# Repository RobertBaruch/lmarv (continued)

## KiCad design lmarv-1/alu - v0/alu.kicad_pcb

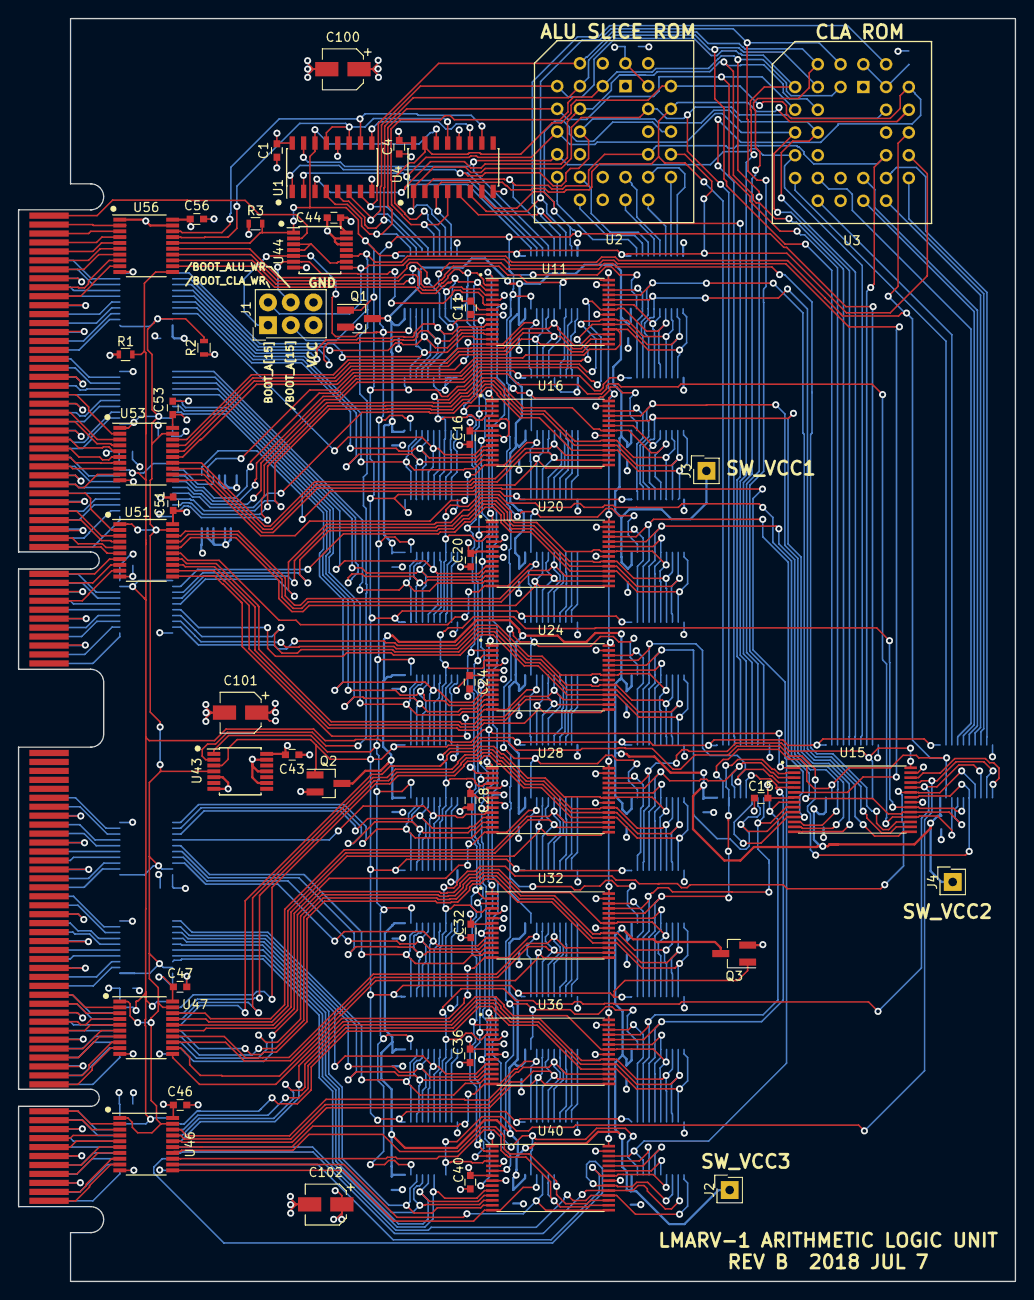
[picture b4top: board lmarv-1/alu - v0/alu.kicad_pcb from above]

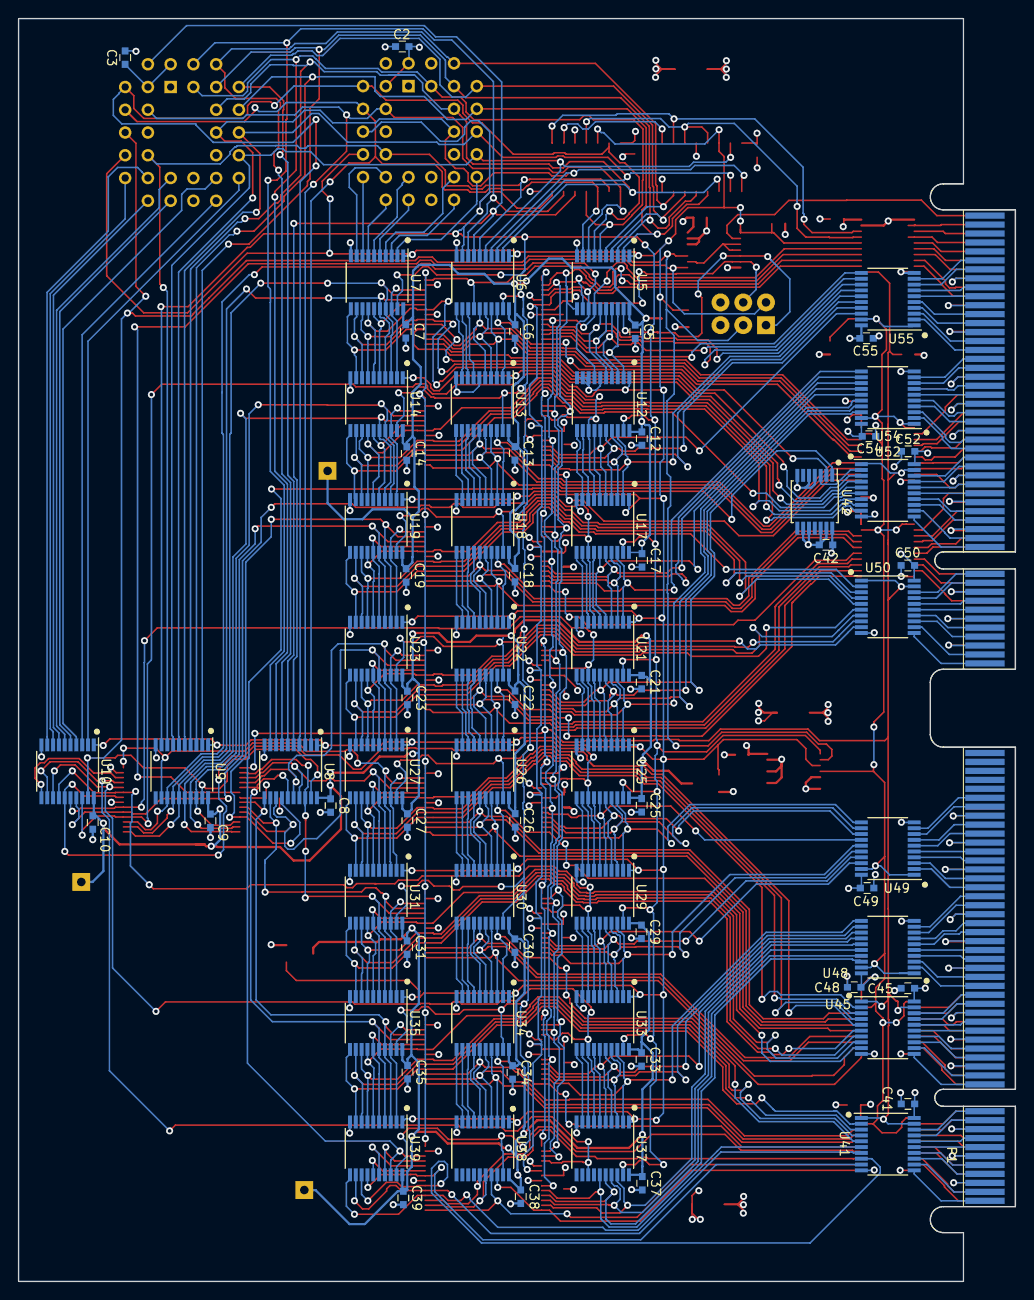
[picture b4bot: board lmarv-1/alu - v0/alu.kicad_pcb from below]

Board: 4 copper layers, 111.3 x 141.0 mm, 126 parts (75 on the bottom side), 339 nets.

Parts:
C1, C2, C3, C4, C5, C6, C7, C8, C9, C10, C11, C12, C13, C14, C15, C16, C17, C18, C19, C20, C21, C22, C23, C24, C25, C26, C27, C28, C29, C30, C31, C32, C33, C34, C35, C36, C37, C38, C39, C40, C41, C42, C43, C44, C45, C46, C47, C48, C49, C50, C51, C52, C53, C54, C55, C56: 0u1; C_0603
C100, C101, C102: 1u; CP_Elec_4x4.5
J1: Conn_02x03_Odd_Even; SDL-106-X-XX_2x03
J2, J3, J4: Conn_01x01; SL-101-X-XX_1x01
P1: dual-pcie-cardedge; PCI-EXPRESS
Q1, Q2, Q3: DMP3056L; SOT-23_Handsoldering
R1, R2, R3: 10k; R_0603
U1, U4: 74HC590; SOIC-16_3.9x9.9mm_Pitch1.27mm
U2: AT28BV64B-20JU; PLCC32
U3: AT28BV256B-20JU; PLCC32
U5, U6, U7, U8, U9, U10, U12, U13, U14, U17, U18, U19, U21, U22, U23, U25, U26, U27, U29, U30, U31, U33, U34, U35, U37, U38, U39, U41, U45, U46, U47, U48, U49, U50, U51, U52, U53, U54, U55, U56: 74LVC541; TSSOP-20_4.4x6.5mm_Pitch0.65mm
U11, U15, U16, U20, U24, U28, U32, U36, U40: IS61LV256AL; TSOP-I-28_18.4x8mm_Pitch0.55mm
U42, U44: 74LVC32; TSSOP-14_4.4x5mm_Pitch0.65mm
U43: 74LVC04; TSSOP-14_4.4x5mm_Pitch0.65mm

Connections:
/BOOT_ALU_EN: R2.2, U43.4, U46.1, U46.19, U47.1, U47.19, U48.1, U48.19, U49.1, U49.19, U51.1, U51.19, U53.1, U53.19, U54.1, U54.19, U55.1, U55.19
/BOOT_A[0]: U1.15, U2.11, U3.11, U6.5, U9.7
/BOOT_A[1]: U1.1, U2.10, U3.10, U6.4, U9.6
/BOOT_A[2]: U1.2, U2.9, U3.9, U6.3, U9.5
/BOOT_A[3]: U1.3, U2.8, U3.8, U6.2, U9.4
/BOOT_A[4]: U1.4, U2.7, U3.7, U5.2, U9.3
/BOOT_A[5]: U1.5, U2.6, U3.6, U5.3, U9.2
/BOOT_A[6]: U1.6, U2.5, U3.5, U5.4, U8.6
/BOOT_A[7]: U1.7, U2.4, U3.4, U5.5, U8.7
/BOOT_A[8]: U2.29, U3.29, U4.15, U5.7, U8.4
/BOOT_A[9]: U2.28, U3.28, U4.1, U5.8, U8.3
/BOOT_A[10]: U2.24, U3.24, U4.2, U6.6, U9.8
/BOOT_A[11]: U2.27, U3.27, U4.3, U5.9, U8.2
/BOOT_A[12]: U2.3, U3.3, U4.4, U5.6, U8.8
/BOOT_A[13]: U3.30, U4.5, U6.7, U8.5
/BOOT_A[14]: U3.2, U4.6, U6.8, U8.9
/BOOT_A[15]: J1.1, U2.25, U4.7, U5.19, U6.9, U6.19, U7.19, U9.9, U12.19, U13.19, U14.19, U17.19, U18.19, U19.19, U21.19, U22.19, U23.19, U25.19, U26.19, U27.19, U29.19, U30.19, U31.19, U33.19, U34.19, U35.19, U37.19, U38.19, U39.19, U43.1, U44.5
/BOOT_CLK: U1.11, U1.13, U4.13, U56.17
/BOOT_CLK': P1.194, U56.3
/CLA_D0: U3.13, U10.2
/CLA_D1: U3.14, U10.3
/CLA_D2: U3.15, U10.4
/CLA_D3: U3.18, U10.5
/CLA_D4: U3.19, U10.6
/CLA_D5: U3.20, U10.7
/CLA_D6: U3.21, U10.8
/CLA_D7: U3.22, U10.9
/SLICE_D0: U2.13, U7.2
/SLICE_D1: U2.14, U7.3
/SLICE_D2: U2.15, U7.4
/SLICE_D3: U2.18, U7.5
/SLICE_D4: U2.19, U7.6
/SLICE_D5: U2.20, U7.7
/SLICE_D6: U2.21, U7.8
/SLICE_D7: U2.22, U7.9
/SW_VCC1: C5.1, C6.1, C7.1, C12.1, C13.1, C14.1, C17.1, C18.1, C19.1, J3.1, Q1.3, U5.20, U6.20, U7.20, U12.20, U13.20, U14.20, U17.20, U18.20, U19.20
/SW_VCC2: C8.1, C9.1, C10.1, C21.1, C22.1, C23.1, C25.1, C26.1, C27.1, J4.1, Q2.3, U8.20, U9.20, U10.20, U21.20, U22.20, U23.20, U25.20, U26.20, U27.20
/SW_VCC3: C29.1, C30.1, C31.1, C33.1, C34.1, C35.1, C37.1, C38.1, C39.1, J2.1, Q3.3, U29.20, U30.20, U31.20, U33.20, U34.20, U35.20, U37.20, U38.20, U39.20
/alu_f[0]: U5.12, U11.24, U16.24, U20.24, U24.24, U28.24, U32.24, U36.24, U40.24, U56.12
/alu_f[1]: U6.14, U11.21, U16.21, U20.21, U24.21, U28.21, U32.21, U36.21, U40.21, U56.13
/alu_f[2]: U5.11, U11.23, U16.23, U20.23, U24.23, U28.23, U32.23, U36.23, U40.23, U56.14
/alu_f[3]: U5.14, U11.2, U16.2, U20.2, U24.2, U28.2, U32.2, U36.2, U40.2, U56.15
/cin[0]: U5.13, U9.13, U11.25, U12.7, U15.10
/cin[1]: U10.18, U12.13, U15.11, U16.25, U17.7
/cin[2]: U10.17, U15.12, U17.13, U20.25, U21.7
/cin[3]: U10.16, U15.13, U21.13, U24.25, U25.7
/cin[4]: U10.15, U15.15, U25.13, U28.25, U29.7
/cin[5]: U10.14, U15.16, U29.13, U32.25, U33.7
/cin[6]: U10.13, U15.17, U33.13, U36.25, U37.7
/cin[7]: U10.12, U15.18, U37.13, U40.25
/cout[0]: U7.15, U11.16, U14.5
/cout[1]: U14.15, U16.16, U19.5
/cout[2]: U19.15, U20.16, U23.5
/cout[3]: U23.15, U24.16, U27.5
/cout[4]: U27.15, U28.16, U31.5
/cout[5]: U31.15, U32.16, U35.5
/cout[6]: U35.15, U36.16, U39.5
/cout[7]: U39.15, U40.16
/f[0]: P1.188, U56.8
/f[1]: P1.190, U56.7
/f[2]: P1.191, U56.6
/f[3]: P1.192, U56.5
/g[0]: U7.17, U9.15, U11.18, U14.3, U15.8
/g[1]: U9.17, U14.17, U15.6, U16.18, U19.3
/g[2]: U8.14, U15.4, U19.17, U20.18, U23.3
/g[3]: U8.16, U15.25, U23.17, U24.18, U27.3
/g[4]: U9.12, U15.21, U27.17, U28.18, U31.3
/g[5]: U8.12, U15.2, U31.17, U32.18, U35.3
/g[6]: U8.11, U15.1, U35.17, U36.18, U39.3
/g[7]: U39.17, U40.18
/lt[0]: U7.18, U11.19, U14.2
/lt[1]: U14.18, U16.19, U19.2
/lt[2]: U19.18, U20.19, U23.2
/lt[3]: U23.18, U24.19, U27.2
/lt[4]: U27.18, U28.19, U31.2
/lt[5]: U31.18, U32.19, U35.2
/lt[6]: U35.18, U36.19, U39.2
/lt[7]: U39.18, U40.19, U42.1
/p[0]: U7.16, U9.14, U11.17, U14.4, U15.9
/p[1]: U9.16, U14.16, U15.7, U16.17, U19.4
/p[2]: U9.18, U15.5, U19.16, U20.17, U23.4
/p[3]: U8.13, U15.3, U23.16, U24.17, U27.4
/p[4]: U8.17, U15.24, U27.16, U28.17, U31.4
/p[5]: U8.18, U15.23, U31.16, U32.17, U35.4
/p[6]: U8.15, U15.26, U35.16, U36.17, U39.4
/p[7]: U39.16, U40.17
/rd[0]: P1.71, U52.18
/rd[1]: P1.70, U52.17
/rd[2]: P1.68, U52.16
/rd[3]: P1.67, U52.15
/rd[4]: P1.65, U52.14
/rd[5]: P1.64, U52.13
/rd[6]: P1.62, U52.12
/rd[7]: P1.61, U52.11
/rd[8]: P1.60, U50.18
/rd[9]: P1.59, U50.17
/rd[10]: P1.57, U50.16
/rd[11]: P1.56, U50.15
/rd[12]: P1.54, U50.14
/rd[13]: P1.53, U50.13
/rd[14]: P1.51, U50.12
/rd[15]: P1.50, U50.11
/rd[16]: P1.22, U45.18
/rd[17]: P1.21, U45.17
/rd[18]: P1.19, U45.16
/rd[19]: P1.18, U45.15
/rd[20]: P1.16, U45.14
/rd[21]: P1.15, U45.13
/rd[22]: P1.13, U45.12
/rd[23]: P1.12, U45.11
/rd[24]: P1.11, U41.18
/rd[25]: P1.10, U41.17
/rd[26]: P1.8, U41.16
/rd[27]: P1.7, U41.15
/rd[28]: P1.5, U41.14
/rd[29]: P1.4, U41.13
/rd[30]: P1.2, U41.12
/rd[31]: P1.1, U41.11
/rdb[0]: U42.3, U52.2
/rdb[0]': U7.11, U11.11, U14.9, U42.2
/rdb[1]: U7.12, U11.12, U14.8, U52.3
/rdb[2]: U7.13, U11.13, U14.7, U52.4
/rdb[3]: U7.14, U11.15, U14.6, U52.5
/rdb[4]: U14.11, U16.11, U19.9, U52.6
/rdb[5]: U14.12, U16.12, U19.8, U52.7
/rdb[6]: U14.13, U16.13, U19.7, U52.8
/rdb[7]: U14.14, U16.15, U19.6, U52.9
/rdb[8]: U19.11, U20.11, U23.9, U50.2
/rdb[9]: U19.12, U20.12, U23.8, U50.3
/rdb[10]: U19.13, U20.13, U23.7, U50.4
/rdb[11]: U19.14, U20.15, U23.6, U50.5
/rdb[12]: U23.11, U24.11, U27.9, U50.6
/rdb[13]: U23.12, U24.12, U27.8, U50.7
/rdb[14]: U23.13, U24.13, U27.7, U50.8
/rdb[15]: U23.14, U24.15, U27.6, U50.9
/rdb[16]: U27.11, U28.11, U31.9, U45.2
/rdb[17]: U27.12, U28.12, U31.8, U45.3
/rdb[18]: U27.13, U28.13, U31.7, U45.4
/rdb[19]: U27.14, U28.15, U31.6, U45.5
/rdb[20]: U31.11, U32.11, U35.9, U45.6
/rdb[21]: U31.12, U32.12, U35.8, U45.7
/rdb[22]: U31.13, U32.13, U35.7, U45.8
/rdb[23]: U31.14, U32.15, U35.6, U45.9
/rdb[24]: U35.11, U36.11, U39.9, U41.2
/rdb[25]: U35.12, U36.12, U39.8, U41.3
/rdb[26]: U35.13, U36.13, U39.7, U41.4
/rdb[27]: U35.14, U36.15, U39.6, U41.5
/rdb[28]: U39.11, U40.11, U41.6
/rdb[29]: U39.12, U40.12, U41.7
/rdb[30]: U39.13, U40.13, U41.8
/rdb[31]: U39.14, U40.15, U41.9
/rs1[0]: P1.176, U53.2
/rs1[1]: P1.174, U53.3
/rs1[2]: P1.173, U53.4
/rs1[3]: P1.171, U53.5
/rs1[4]: P1.170, U53.6
/rs1[5]: P1.169, U53.7
/rs1[6]: P1.168, U53.8
/rs1[7]: P1.166, U53.9
/rs1[8]: P1.165, U51.2
/rs1[9]: P1.163, U51.3
/rs1[10]: P1.162, U51.4
/rs1[11]: P1.160, U51.5
/rs1[12]: P1.159, U51.6
/rs1[13]: P1.158, U51.7
/rs1[14]: P1.157, U51.8
/rs1[15]: P1.155, U51.9
/rs1[16]: P1.120, U47.2
/rs1[17]: P1.119, U47.3
/rs1[18]: P1.117, U47.4
/rs1[19]: P1.116, U47.5
/rs1[20]: P1.114, U47.6
/rs1[21]: P1.113, U47.7
/rs1[22]: P1.111, U47.8
/rs1[23]: P1.110, U47.9
/rs1[24]: P1.109, U46.2
/rs1[25]: P1.108, U46.3
/rs1[26]: P1.106, U46.4
/rs1[27]: P1.105, U46.5
/rs1[28]: P1.103, U46.6
/rs1[29]: P1.102, U46.7
/rs1[30]: P1.100, U46.8
/rs1[31]: P1.99, U46.9
/rs1b[0]: U6.15, U11.10, U13.5, U53.18
/rs1b[1]: U6.16, U11.9, U13.4, U53.17
/rs1b[2]: U6.17, U11.8, U13.3, U53.16
/rs1b[3]: U6.18, U11.7, U13.2, U53.15
/rs1b[4]: U13.15, U16.10, U18.5, U53.14
/rs1b[5]: U13.16, U16.9, U18.4, U53.13
/rs1b[6]: U13.17, U16.8, U18.3, U53.12
/rs1b[7]: U13.18, U16.7, U18.2, U53.11
/rs1b[8]: U18.15, U20.10, U22.5, U51.18
/rs1b[9]: U18.16, U20.9, U22.4, U51.17
/rs1b[10]: U18.17, U20.8, U22.3, U51.16
/rs1b[11]: U18.18, U20.7, U22.2, U51.15
/rs1b[12]: U22.15, U24.10, U26.5, U51.14
/rs1b[13]: U22.16, U24.9, U26.4, U51.13
/rs1b[14]: U22.17, U24.8, U26.3, U51.12
/rs1b[15]: U22.18, U24.7, U26.2, U51.11
/rs1b[16]: U26.15, U28.10, U30.5, U47.18
/rs1b[17]: U26.16, U28.9, U30.4, U47.17
/rs1b[18]: U26.17, U28.8, U30.3, U47.16
/rs1b[19]: U26.18, U28.7, U30.2, U47.15
/rs1b[20]: U30.15, U32.10, U34.5, U47.14
/rs1b[21]: U30.16, U32.9, U34.4, U47.13
/rs1b[22]: U30.17, U32.8, U34.3, U47.12
/rs1b[23]: U30.18, U32.7, U34.2, U47.11
/rs1b[24]: U34.15, U36.10, U38.5, U46.18
/rs1b[25]: U34.16, U36.9, U38.4, U46.17
/rs1b[26]: U34.17, U36.8, U38.3, U46.16
/rs1b[27]: U34.18, U36.7, U38.2, U46.15
/rs1b[28]: U38.15, U40.10, U46.14
/rs1b[29]: U38.16, U40.9, U46.13
/rs1b[30]: U38.17, U40.8, U46.12
/rs1b[31]: U38.18, U40.7, U46.11
/rs2[0]: P1.93, U55.9
/rs2[1]: P1.92, U55.8
/rs2[2]: P1.90, U55.7
/rs2[3]: P1.89, U55.6
/rs2[4]: P1.87, U55.5
/rs2[5]: P1.86, U55.4
/rs2[6]: P1.84, U55.3
/rs2[7]: P1.83, U55.2
/rs2[8]: P1.82, U54.9
/rs2[9]: P1.81, U54.8
/rs2[10]: P1.79, U54.7
/rs2[11]: P1.78, U54.6
/rs2[12]: P1.76, U54.5
/rs2[13]: P1.75, U54.4
/rs2[14]: P1.73, U54.3
/rs2[15]: P1.72, U54.2
/rs2[16]: P1.44, U49.9
/rs2[17]: P1.43, U49.8
/rs2[18]: P1.41, U49.7
/rs2[19]: P1.40, U49.6
/rs2[20]: P1.38, U49.5
/rs2[21]: P1.37, U49.4
/rs2[22]: P1.35, U49.3
/rs2[23]: P1.34, U49.2
/rs2[24]: P1.33, U48.9
/rs2[25]: P1.32, U48.8
/rs2[26]: P1.30, U48.7
/rs2[27]: P1.29, U48.6
/rs2[28]: P1.27, U48.5
/rs2[29]: P1.26, U48.4
/rs2[30]: P1.24, U48.3
/rs2[31]: P1.23, U48.2
/rs2b[0]: U5.18, U11.6, U12.2, U55.11
/rs2b[1]: U5.17, U11.5, U12.3, U55.12
/rs2b[2]: U5.16, U11.4, U12.4, U55.13
/rs2b[3]: U5.15, U11.3, U12.5, U55.14
/rs2b[4]: U12.18, U16.6, U17.2, U55.15
/rs2b[5]: U12.17, U16.5, U17.3, U55.16
/rs2b[6]: U12.16, U16.4, U17.4, U55.17
/rs2b[7]: U12.15, U16.3, U17.5, U55.18
/rs2b[8]: U17.18, U20.6, U21.2, U54.11
/rs2b[9]: U17.17, U20.5, U21.3, U54.12
/rs2b[10]: U17.16, U20.4, U21.4, U54.13
/rs2b[11]: U17.15, U20.3, U21.5, U54.14
/rs2b[12]: U21.18, U24.6, U25.2, U54.15
/rs2b[13]: U21.17, U24.5, U25.3, U54.16
/rs2b[14]: U21.16, U24.4, U25.4, U54.17
/rs2b[15]: U21.15, U24.3, U25.5, U54.18
/rs2b[16]: U25.18, U28.6, U29.2, U49.11
/rs2b[17]: U25.17, U28.5, U29.3, U49.12
/rs2b[18]: U25.16, U28.4, U29.4, U49.13
/rs2b[19]: U25.15, U28.3, U29.5, U49.14
/rs2b[20]: U29.18, U32.6, U33.2, U49.15
/rs2b[21]: U29.17, U32.5, U33.3, U49.16
/rs2b[22]: U29.16, U32.4, U33.4, U49.17
/rs2b[23]: U29.15, U32.3, U33.5, U49.18
/rs2b[24]: U33.18, U36.6, U37.2, U48.11
/rs2b[25]: U33.17, U36.5, U37.3, U48.12
/rs2b[26]: U33.16, U36.4, U37.4, U48.13
/rs2b[27]: U33.15, U36.3, U37.5, U48.14
/rs2b[28]: U37.18, U40.6, U48.15
/rs2b[29]: U37.17, U40.5, U48.16
/rs2b[30]: U37.16, U40.4, U48.17
/rs2b[31]: U37.15, U40.3, U48.18
/~BOOT_ALU_EN: Q1.1, Q2.1, Q3.1, R3.2, U1.14, U2.23, U3.23, U4.14, U5.1, U6.1, U7.1, U8.1, U9.1, U10.1, U12.1, U13.1, U14.1, U17.1, U18.1, U19.1, U21.1, U22.1, U23.1, U25.1, U26.1, U27.1, U29.1, U30.1, U31.1, U33.1, U34.1, U35.1, U37.1, U38.1, U39.1, U43.3, U44.1, U56.16
/~BOOT_ALU_EN': P1.193, U56.4
/~BOOT_ALU_WR: J1.4, U11.27, U16.27, U20.27, U24.27, U28.27, U32.27, U36.27, U40.27, U44.6
/~BOOT_ALU_WR': U44.3, U44.4, U44.9
/~BOOT_A[15]: J1.3, U3.25, U8.19, U9.19, U10.19, U43.2, U44.10
/~BOOT_CLA_WR: J1.2, U15.27, U44.8
/~BOOT_RCO: U1.9, U4.11
/~BOOT_RST: U1.10, U4.10, U56.18
/~BOOT_RST': P1.195, U56.2
/~BOOT_WR: P1.196, U44.2
/~alu_oe: R1.2, U11.22, U15.22, U16.22, U20.22, U24.22, U28.22, U32.22, U36.22, U40.22, U41.1, U41.19, U45.1, U45.19, U50.1, U50.19, U52.1, U52.19, U56.11
/~alu_oe': P1.187, U56.9
GND: C1.2, C2.2, C3.2, C4.2, C5.2, C6.2, C7.2, C8.2, C9.2, C10.2, C11.2, C12.2, C13.2, C14.2, C15.2, C16.2, C17.2, C18.2, C19.2, C20.2, C21.2, C22.2, C23.2, C24.2, C25.2, C26.2, C27.2, C28.2, C29.2, C30.2, C31.2, C32.2, C33.2, C34.2, C35.2, C36.2, C37.2, C38.2, C39.2, C40.2, C41.2, C42.2, C43.2, C44.2, C45.2, C46.2, C47.2, C48.2, C49.2, C50.2, C51.2, C52.2, C53.2, C54.2, C55.2, C56.2, C100.2, C101.2, C102.2, J1.6, P1.3, P1.9, P1.14, P1.20, P1.25, P1.31, P1.36, P1.42, P1.52, P1.58, P1.63, P1.69, P1.74, P1.80, P1.85, P1.91, P1.101, P1.107, P1.112, P1.118, P1.123, P1.129, P1.134, P1.140, P1.150, P1.156, P1.161, P1.167, P1.172, P1.178, P1.183, P1.189, U1.8, U1.12, U2.16, U3.16, U4.8, U4.12, U5.10, U6.10, U7.10, U8.10, U9.10, U10.10, U11.1, U11.14, U11.20, U11.26, U12.6, U12.8, U12.9, U12.10, U13.6, U13.10, U14.10, U15.14, U15.20, U16.1, U16.14, U16.20, U16.26, U17.10, U18.10, U19.10, U20.1, U20.14, U20.20, U20.26, U21.10, U22.10, U23.10, U24.1, U24.14, U24.20, U24.26, U25.10, U26.10, U27.10, U28.1, U28.14, U28.20, U28.26, U29.10, U30.10, U31.10, U32.1, U32.14, U32.20, U32.26, U33.10, U34.10, U35.10, U36.1, U36.14, U36.20, U36.26, U37.10, U38.10, U39.10, U40.1, U40.14, U40.20, U40.26, U41.10, U42.4, U42.5, U42.7, U42.9, U42.10, U42.12, U42.13, U43.5, U43.7, U43.9, U43.11, U43.13, U44.7, U44.12, U44.13, U45.10, U46.10, U47.10, U48.10, U49.10, U50.10, U51.10, U52.10, U53.10, U54.10, U55.10, U56.1, U56.10, U56.19
unnamed: U10.11, U15.19
unnamed: U12.11, U17.9
unnamed: U12.12, U17.8
unnamed: U12.14, U17.6
unnamed: U6.13, U13.7
unnamed: U6.12, U13.8
unnamed: U6.11, U13.9
unnamed: U13.11, U18.9
unnamed: U13.12, U18.8
unnamed: U13.13, U18.7
unnamed: U13.14, U18.6
unnamed: U17.11, U21.9
unnamed: U17.12, U21.8
unnamed: U17.14, U21.6
unnamed: U18.11, U22.9
unnamed: U18.12, U22.8
unnamed: U18.13, U22.7
unnamed: U18.14, U22.6
unnamed: U21.11, U25.9
unnamed: U21.12, U25.8
unnamed: U21.14, U25.6
unnamed: U22.11, U26.9
unnamed: U22.12, U26.8
unnamed: U22.13, U26.7
unnamed: U22.14, U26.6
unnamed: U25.11, U29.9
unnamed: U25.12, U29.8
unnamed: U25.14, U29.6
unnamed: U26.11, U30.9
unnamed: U26.12, U30.8
unnamed: U26.13, U30.7
unnamed: U26.14, U30.6
unnamed: U29.11, U33.9
unnamed: U29.12, U33.8
unnamed: U29.14, U33.6
unnamed: U30.11, U34.9
unnamed: U30.12, U34.8
unnamed: U30.13, U34.7
unnamed: U30.14, U34.6
unnamed: U33.11, U37.9
unnamed: U33.12, U37.8
unnamed: U33.14, U37.6
unnamed: U34.11, U38.9
unnamed: U34.12, U38.8
unnamed: U34.13, U38.7
unnamed: U34.14, U38.6
VCC: C1.1, C2.1, C3.1, C4.1, C11.1, C15.1, C16.1, C20.1, C24.1, C28.1, C32.1, C36.1, C40.1, C41.1, C42.1, C43.1, C44.1, C45.1, C46.1, C47.1, C48.1, C49.1, C50.1, C51.1, C52.1, C53.1, C54.1, C55.1, C56.1, C100.1, C101.1, C102.1, J1.5, P1.6, P1.17, P1.28, P1.39, P1.55, P1.66, P1.77, P1.88, P1.104, P1.115, P1.126, P1.137, P1.153, P1.164, P1.175, P1.186, Q1.2, Q2.2, Q3.2, R1.1, R2.1, R3.1, U1.16, U2.31, U2.32, U3.31, U3.32, U4.16, U11.28, U15.28, U16.28, U20.28, U24.28, U28.28, U32.28, U36.28, U40.28, U41.20, U42.14, U43.14, U44.14, U45.20, U46.20, U47.20, U48.20, U49.20, U50.20, U51.20, U52.20, U53.20, U54.20, U55.20, U56.20
